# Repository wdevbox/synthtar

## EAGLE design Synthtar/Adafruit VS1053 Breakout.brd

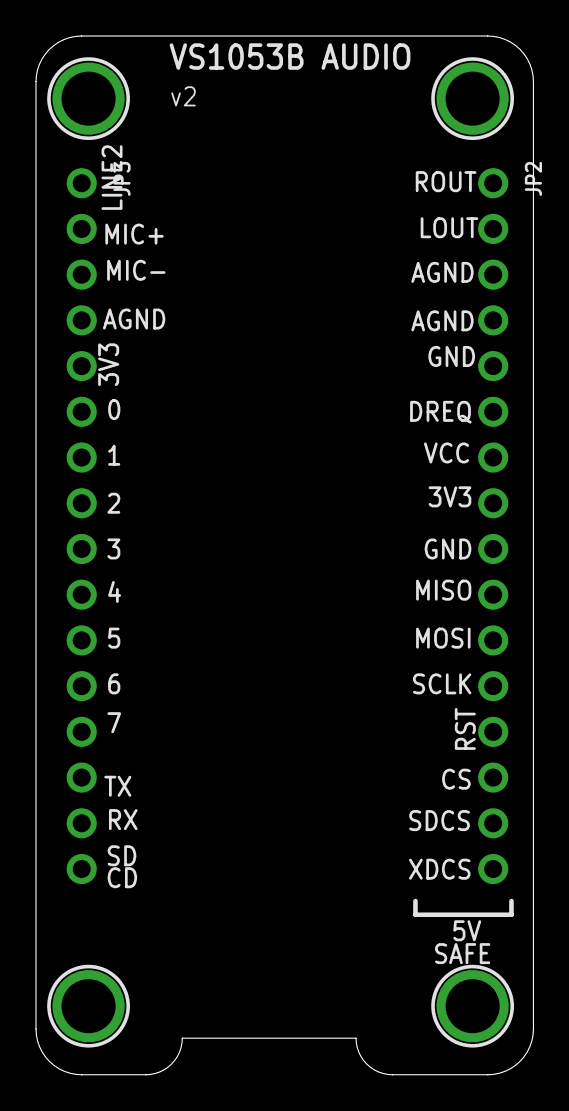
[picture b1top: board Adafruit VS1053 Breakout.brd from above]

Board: 2 copper layers, 27.6 x 57.7 mm, 7 parts (1 on the bottom side), 2 nets, no tracks yet.

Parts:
JP2, JP3: 1X16_ROUND
U$50, U$51, U$52, U$53: MOUNTINGHOLE3.0THIN; MOUNTINGHOLE_3.0_PLATEDTHIN
U$55: ADAFRUIT_TEXT_20MM

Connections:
AGND: JP2.3, JP2.4
GND: JP2.5, JP2.9

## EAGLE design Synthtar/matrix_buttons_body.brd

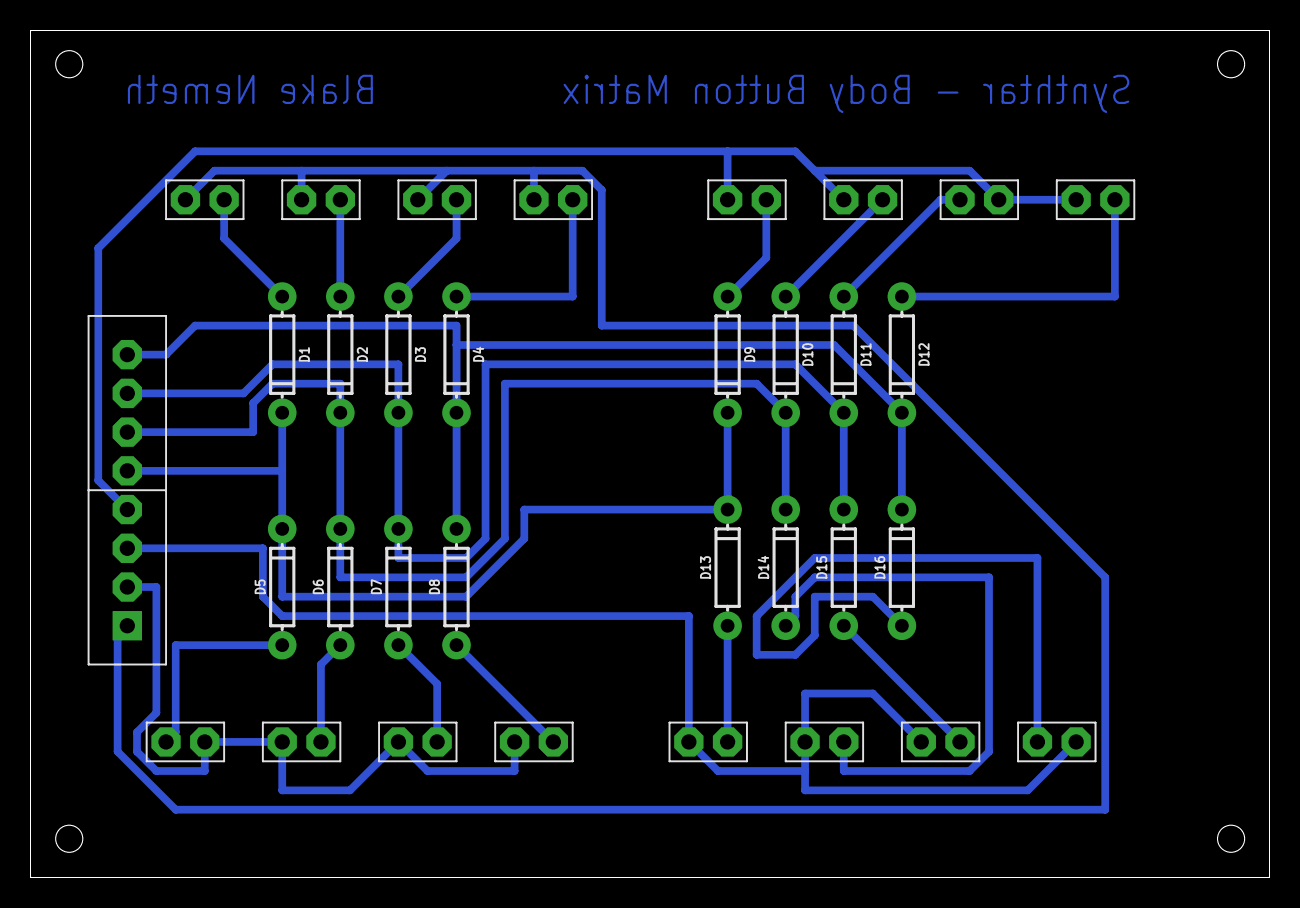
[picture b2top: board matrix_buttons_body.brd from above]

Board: 2 copper layers, 81.3 x 55.5 mm, 33 parts (0 on the bottom side), 24 nets.

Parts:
D1, D2, D3, D4, D5, D6, D7, D8, D9, D10, D11, D12, D13, D14, D15, D16: 200mA/100V/1V; DIODE-1N4148
U$1, U$2, U$3, U$4, U$5, U$6, U$7, U$8, U$9, U$10, U$11, U$12, U$13, U$14, U$15, U$16: 2-PIN-HEADER
U$17: 8-PIN-HEADER

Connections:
ADD_BTNS: U$9.P$1, U$10.P$1, U$11.P$1, U$12.P$1, U$17.P$4
BODY_BTNS: U$1.P$1, U$2.P$1, U$3.P$1, U$4.P$1, U$17.P$1
B_ROW_1: D1.C, D5.C, D9.C, D13.C, U$17.P$5
B_ROW_2: D2.C, D6.C, D10.C, D14.C, U$17.P$6
B_ROW_3: D3.C, D7.C, D11.C, D15.C, U$17.P$7
B_ROW_4: D4.C, D8.C, D12.C, D16.C, U$17.P$8
MENU_BTNS: U$5.P$1, U$6.P$1, U$7.P$1, U$8.P$1, U$17.P$2
unnamed: D11.A, U$11.P$2
unnamed: D12.A, U$12.P$2
unnamed: D9.A, U$9.P$2
unnamed: D10.A, U$10.P$2
unnamed: D5.A, U$5.P$2
unnamed: D6.A, U$6.P$2
unnamed: D7.A, U$7.P$2
unnamed: D8.A, U$8.P$2
unnamed: D1.A, U$1.P$2
unnamed: D2.A, U$2.P$2
unnamed: D3.A, U$3.P$2
unnamed: D4.A, U$4.P$2
unnamed: D13.A, U$13.P$2
unnamed: D14.A, U$14.P$2
unnamed: D15.A, U$15.P$2
unnamed: D16.A, U$16.P$2
QUIK_BTNS: U$13.P$1, U$14.P$1, U$15.P$1, U$16.P$1, U$17.P$3

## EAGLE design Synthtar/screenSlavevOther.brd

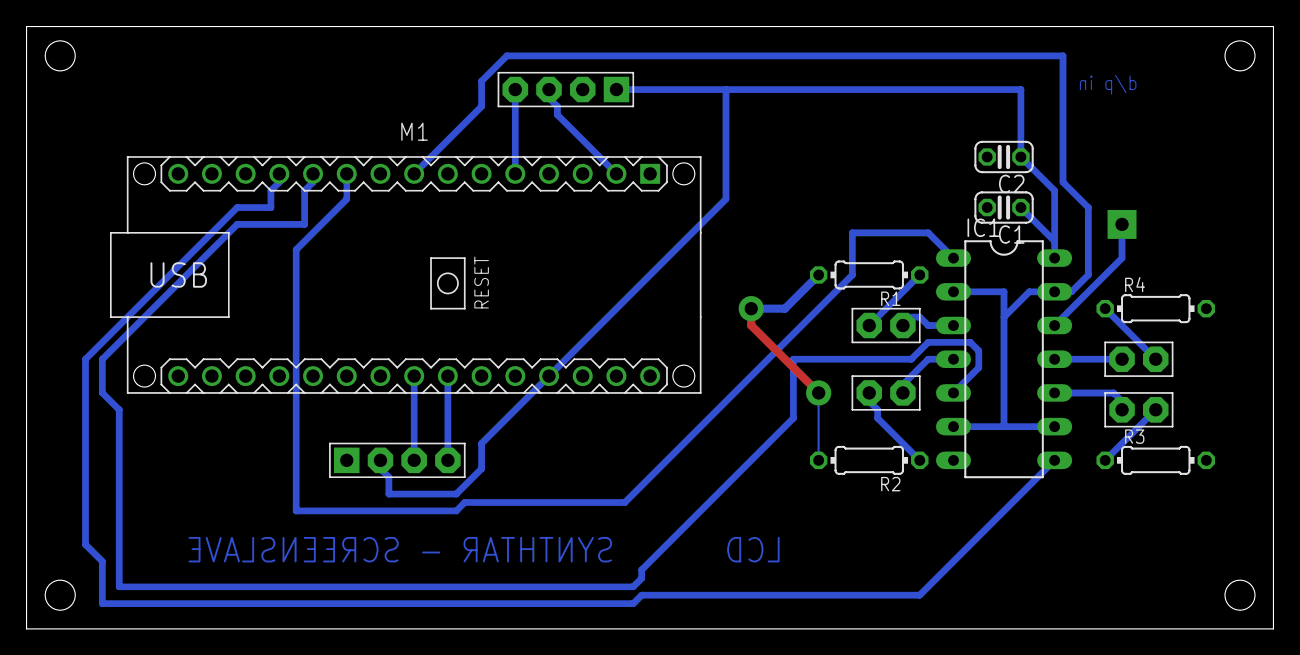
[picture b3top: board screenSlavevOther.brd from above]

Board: 2 copper layers, 94.0 x 45.4 mm, 15 parts (0 on the bottom side), 19 nets.

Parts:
C1: .01uF; C025-024X044
C2: .1uF; C025-024X044
IC1: 4081N; DIL14
M1: ARDUINO-NANO-3.0
R1, R2, R3, R4: 400; 0204/7
U$1, U$2: 4-PIN-HEADER
U$3: 1-PIN-HEADER
U$4, U$5, U$6, U$7: 2-PIN-HEADER

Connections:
+5V: C1.1, C2.1, IC1.14, M1.J2.4, U$1.P$1, U$2.P$2
BUSY_OUT: M1.J1.5, U$1.P$4
DATA_IN: M1.J1.2, U$1.P$3
GND: C1.2, C2.2, IC1.7, M1.J2.2, R1.2, R2.2, R3.2, R4.2, U$1.P$2, U$2.P$1
unnamed: IC1.12, U$3.P$1
unnamed: IC1.11, U$7.P$1
unnamed: IC1.3, U$4.P$1
unnamed: R1.1, U$4.P$2
unnamed: IC1.4, U$5.P$1
unnamed: IC1.10, U$6.P$1
unnamed: R3.1, U$6.P$2
unnamed: IC1.1, M1.J1.10
unnamed: R2.1, U$5.P$2
unnamed: IC1.5, M1.J1.11
unnamed: IC1.8, M1.J1.12
unnamed: R4.1, U$7.P$2
SCL: M1.J2.7, U$2.P$4
SDA: M1.J2.8, U$2.P$3
SIG_PWM: IC1.2, IC1.6, IC1.9, IC1.13, M1.J1.8

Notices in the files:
parts and their libraries:
SparkFun-DiscreteSemi: Licensing: Creative Commons ShareAlike 4.0 International - https://creativecommons.org/licenses/by-sa/4.0
diy-modules: Released under the Creative Commons Attribution 4.0 International License: http://creativecommons.org/licenses/by/4.0
